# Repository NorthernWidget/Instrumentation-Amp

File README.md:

# Instrumentation-Amp

Breakout board for the AD623 instrumentation amplifier.

It is set up to work in either single-supply or dual-supply mode

## Single-supply mode

* Connect VC- (negative supply voltage) to GND using JP_VC- or the screw terminals

For sensors that require a simple common ground (including the reference), you will close the circuit across all of the solder jumpers:
* Connect VS- (negative voltage from device with signal to be amplified) to GND using JP_VS- or the screw terminals
* Connect Vref (reference voltage for the input signal) to GND using JP_VREF or the screw terminals

We use connect all of the jumpers to use a pyranometer.

### Dual-supply mode

We haven't had to use the board this way, but set it up to work!

* Disconnect VC- (negative supply voltage) from GND: check JP_VC- and the screw terminals
* Disconnect VS- (negative voltage from device with signal to be amplified) from GND: check JP_VS- and the screw terminals

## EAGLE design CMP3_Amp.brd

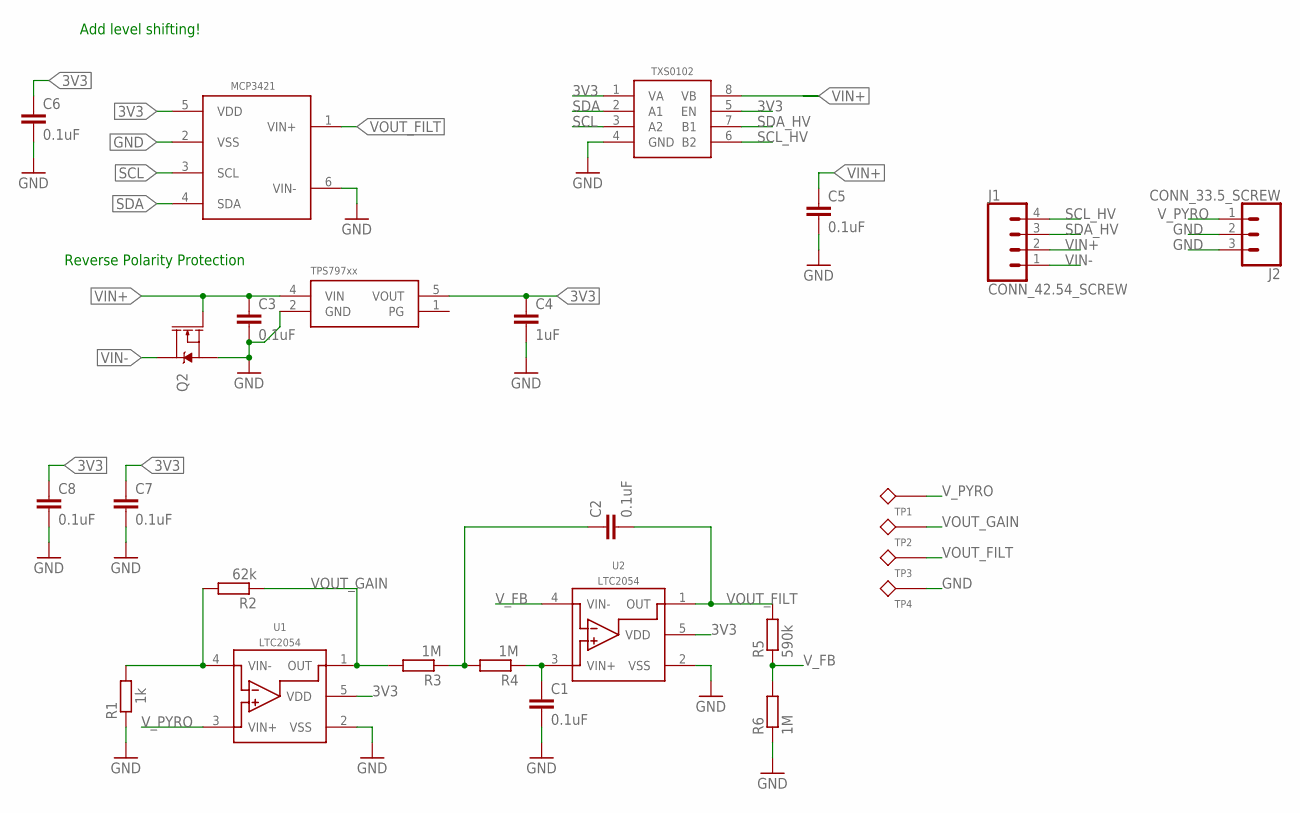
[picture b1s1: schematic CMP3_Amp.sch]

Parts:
C1, C2, C3: 0.1uF; C0603
C4: 1uF; C0603
C5, C6, C7, C8: 0.1uF; C0402
J1: CONN_42.54_SCREW; 1X04_SCREW
J2: CONN_33.5_SCREW; 1X03_3.5MM_SCREW
Q2: DMG3404; SOT23-3
R1: 1k; R0603
R2: 62k; R0603
R3, R4, R6: 1M; R0603
R5: 590k; R0603
TP1, TP2, TP3, TP4: TESTPOINTRCU; TESTPOINT_0603
U1, U2: LTC2054; SOT23-5
U3: MCP3421A1; SOT23-6L
U4: TXS0102DQM; DQM_R-PX2SON-N8
U5: TPS79733; DCK_R-PDSO-G5

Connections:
3V3: C4.1, C6.1, C7.1, C8.1, U1.5 (VDD), U2.5 (VDD), U3.5 (VDD), U4.1 (VA), U4.5 (EN), U5.5 (VOUT)
GND: C1.2, C3.2, C4.2, C5.2, C6.2, C7.2, C8.2, J2.2, J2.3, Q2.2 (S), R1.1, R6.1, TP4.1, U1.2 (VSS), U2.2 (VSS), U3.2 (VSS), U3.6 (VIN-), U4.4 (GND), U5.2 (GND)
unnamed: R1.2, R2.2, U1.4 (VIN-)
unnamed: C2.1, R3.1, R4.2
unnamed: C1.1, R4.1, U2.3 (VIN+)
SCL: U3.3 (SCL), U4.3 (A2)
SCL_HV: J1.4, U4.6 (B2)
SDA: U3.4 (SDA), U4.2 (A1)
SDA_HV: J1.3, U4.7 (B1)
VIN+: C3.1, C5.1, J1.2, Q2.1 (G), U4.8 (VB), U5.4 (VIN)
VIN-: J1.1, Q2.3 (D)
VOUT_FILT: C2.2, R5.2, TP3.1, U2.1 (OUT), U3.1 (VIN+)
VOUT_GAIN: R2.1, R3.2, TP2.1, U1.1 (OUT)
V_FB: R5.1, R6.2, U2.4 (VIN-)
V_PYRO: J2.1, TP1.1, U1.3 (VIN+)

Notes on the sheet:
Reverse Polarity Protection
Add level shifting!

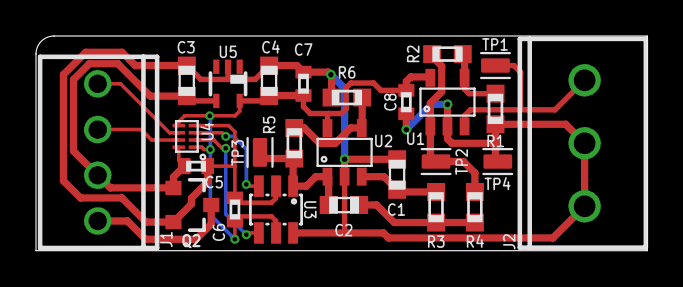
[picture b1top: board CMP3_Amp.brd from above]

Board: 2 copper layers, 34.0 x 11.9 mm, 26 parts (0 on the bottom side), 15 nets.

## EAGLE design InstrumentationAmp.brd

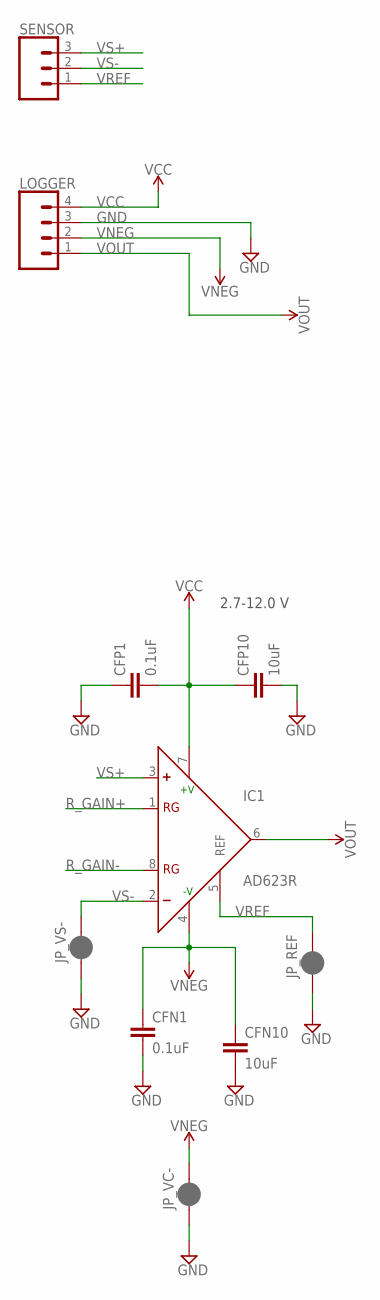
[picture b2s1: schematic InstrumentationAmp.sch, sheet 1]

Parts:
CFN1: 0.1uF; 0603
CFN10: 10uF; C0805
CFP1: 0.1uF; 0603
CFP10: 10uF; C0805
IC1: AD623R; SO8
JP_REF: JUMPER-SMT_2_NC_PASTE_SILK; SMT-JUMPER_2_NC_PASTE_SILK
JP_VC-: JUMPER-SMT_2_NC_PASTE_SILK; SMT-JUMPER_2_NC_PASTE_SILK
JP_VS-: JUMPER-SMT_2_NC_PASTE_SILK; SMT-JUMPER_2_NC_PASTE_SILK
LOGGER: CONN_04; 1X04
SENSOR: CONN_03; 1X03

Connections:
GND: CFN1.2, CFN10.2, CFP1.1, CFP10.2, JP_REF.1, JP_VC-.1, JP_VS-.1, LOGGER.3; also elsewhere on the board
R_GAIN+: IC1.1 (RG); also elsewhere on the board
R_GAIN-: IC1.8 (RG); also elsewhere on the board
VCC: CFP1.2, CFP10.1, IC1.7 (+V), LOGGER.4; also elsewhere on the board
VNEG: CFN1.1, CFN10.1, IC1.4 (-V), JP_VC-.2, LOGGER.2
VOUT: IC1.6 (OUT), LOGGER.1
VREF: IC1.5 (REF), JP_REF.2, SENSOR.1
VS+: IC1.3 (+), SENSOR.3
VS-: IC1.2 (-), JP_VS-.2, SENSOR.2

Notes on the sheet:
2.7-12.0 V

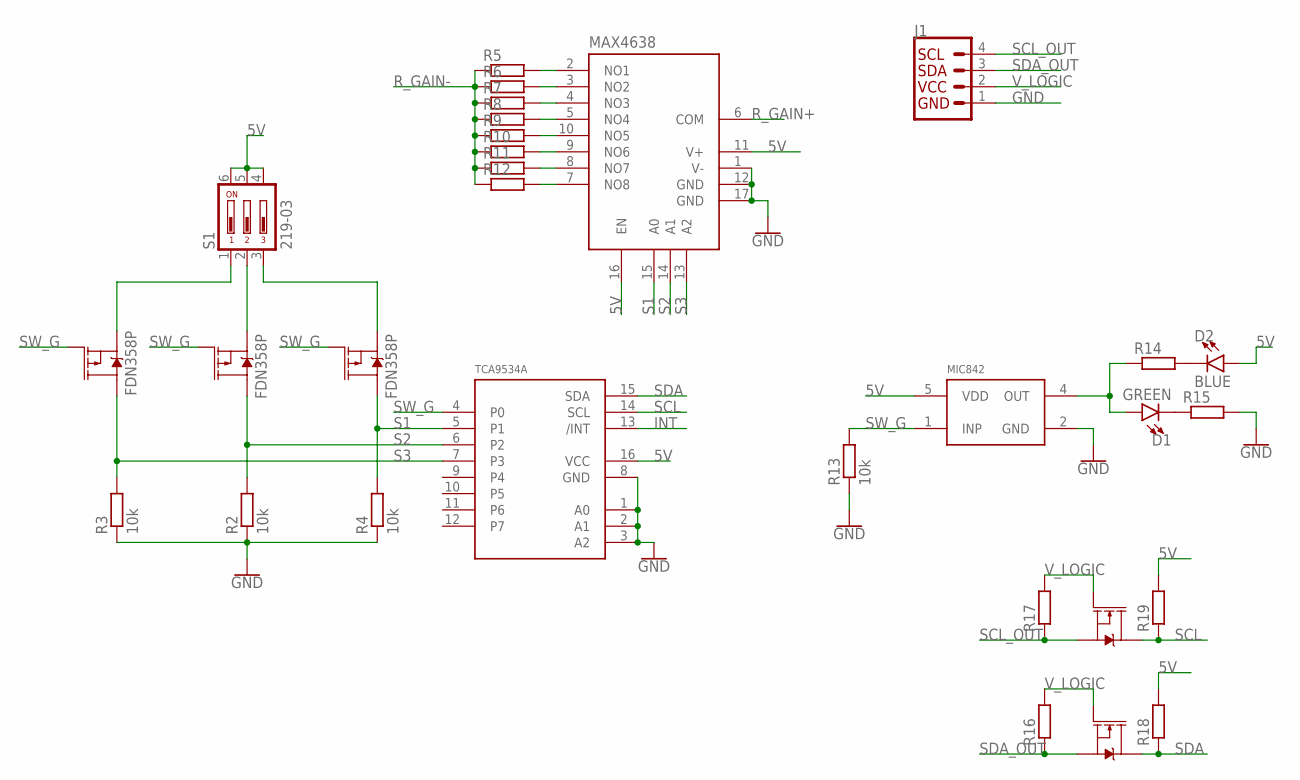
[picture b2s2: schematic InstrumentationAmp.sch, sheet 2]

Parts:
D1: GREEN; LED-0603
D2: BLUE; LED-0603
J1: I2C_STANDARD; 1X04
Q1, Q2: 310mA/60V/1.6Ω; SOT323
R2, R3, R4, R13: 10k; R0603
R5, R6, R7, R8, R9, R10, R11, R12, R14, R15, R16, R17, R18, R19: R-EU_R0603; R0603
S1: 219-03; CTS-219-03
U$1: MAX4638; TQFN16
U$2: TCA9534A; TSSOP16
U$3, U$4, U$5: FDN358P; SSOT-3
U$6: MIC842; DCK_R-PDSO-G5

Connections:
5V: D2.A, R18.2, R19.2, S1.4, S1.5, S1.6, U$1.11 (V+), U$1.16 (EN), U$2.16 (VCC), U$6.5 (VDD); also elsewhere on the board
GND: J1.1, R2.1, R3.1, R4.1, R13.1, R15.2, U$1.1 (V-), U$1.12 (GND), U$1.17 (GND), U$2.1 (A0), U$2.2 (A1), U$2.3 (A2), U$2.8 (GND), U$6.2 (GND); also elsewhere on the board
INT: U$2.13 (/INT)
unnamed: S1.2, U$4.2 (S)
unnamed: D2.C, R14.2
unnamed: S1.3, U$5.2 (S)
unnamed: S1.1, U$3.2 (S)
unnamed: R5.2, U$1.2 (NO1)
unnamed: R6.2, U$1.3 (NO2)
unnamed: R7.2, U$1.4 (NO3)
unnamed: R8.2, U$1.5 (NO4)
unnamed: R9.2, U$1.10 (NO5)
unnamed: R10.2, U$1.9 (NO6)
unnamed: R11.2, U$1.8 (NO7)
unnamed: R12.2, U$1.7 (NO8)
unnamed: D1.C, R15.1
unnamed: D1.A, R14.1, U$6.4 (OUT)
R_GAIN+: U$1.6 (COM); also elsewhere on the board
R_GAIN-: R5.1, R6.1, R7.1, R8.1, R9.1, R10.1, R11.1, R12.1; also elsewhere on the board
S1: R4.2, U$1.15 (A0), U$2.5 (P1), U$5.3 (D)
S2: R2.2, U$1.14 (A1), U$2.6 (P2), U$4.3 (D)
S3: R3.2, U$1.13 (A2), U$2.7 (P3), U$3.3 (D)
SCL: Q2.3 (D), R19.1, U$2.14 (SCL)
SCL_OUT: J1.4, Q2.2 (S), R17.1
SDA: Q1.3 (D), R18.1, U$2.15 (SDA)
SDA_OUT: J1.3, Q1.2 (S), R16.1
SW_G: R13.2, U$2.4 (P0), U$3.1 (G), U$4.1 (G), U$5.1 (G), U$6.1 (INP)
V_LOGIC: J1.2, Q1.1 (G), Q2.1 (G), R16.2, R17.2

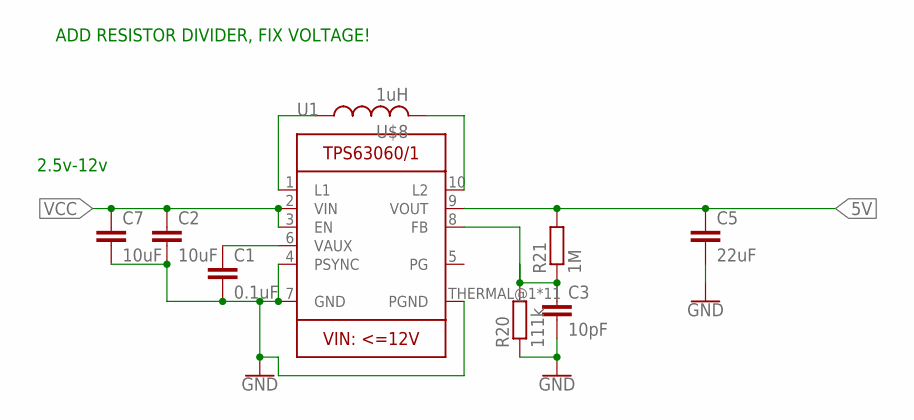
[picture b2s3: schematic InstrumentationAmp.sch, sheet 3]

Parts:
C1: 0.1uF; C0603
C2, C7: 10uF; C0805
C3: 10pF; C0603
C5: 22uF; C0805
R20: 111k; R0603
R21: 1M; R0603
U1: TPS63061; PWSON-N10
U$8: 1uH; WE-MAIA(4.1X4.1)

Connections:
5V: C5.1, R21.2, U1.9 (VOUT); also elsewhere on the board
GND: C1.2, C2.2, C3.2, C5.2, C7.2, R20.1, U1.4 (PSYNC), U1.7 (GND), U1.THERMAL@1 (PGND), U1.THERMAL@5 (PGND), U1.THERMAL@6 (PGND), U1.THERMAL@7 (PGND), U1.THERMAL@8 (PGND), U1.THERMAL@9 (PGND), U1.THERMAL@10 (PGND), U1.THERMAL@11 (PGND), U1.THERMAL@12 (PGND), U1.THERMAL@13 (PGND), U1.THERMAL@14 (PGND); also elsewhere on the board
unnamed: U1.1 (L1), U$8.P$1 (1)
unnamed: C3.1, R20.2, R21.1, U1.8 (FB)
unnamed: U1.10 (L2), U$8.P$2 (2)
unnamed: C1.1, U1.6 (VAUX)
VCC: C2.1, C7.1, U1.2 (VIN), U1.3 (EN); also elsewhere on the board

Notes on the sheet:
2.5v-12v
ADD RESISTOR DIVIDER, FIX VOLTAGE!

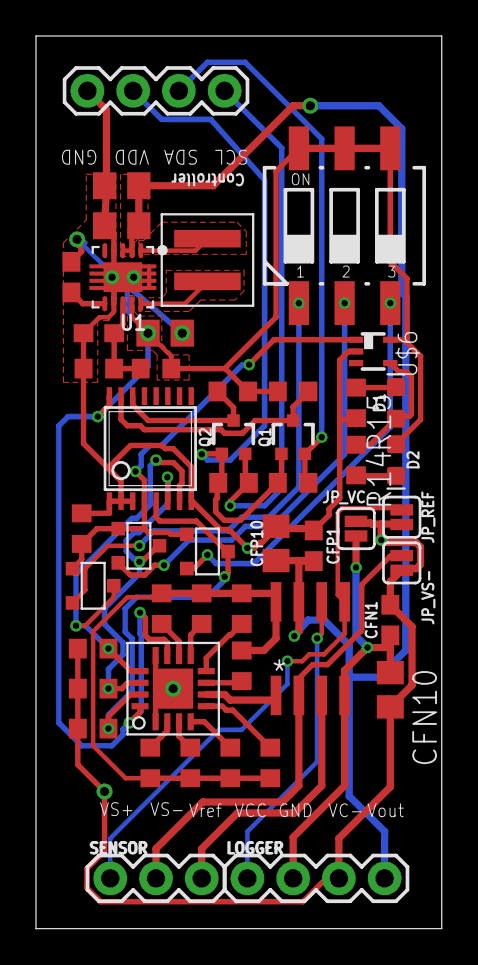
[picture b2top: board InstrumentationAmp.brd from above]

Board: 2 copper layers, 22.5 x 49.6 mm, 49 parts (0 on the bottom side), 37 nets.

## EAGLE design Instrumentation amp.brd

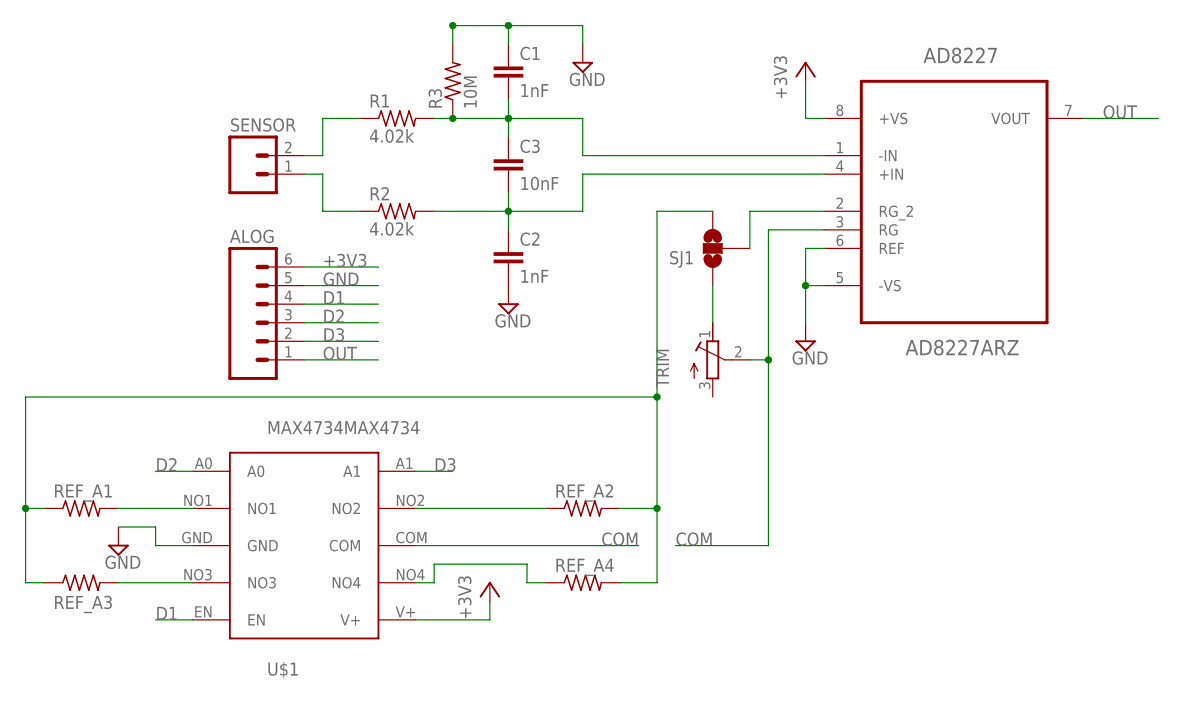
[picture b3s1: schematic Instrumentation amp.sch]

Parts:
AD8227: AD8227ARZ; SOIC127P600X175-8N
ALOG: M063.5MM-6; SCREWTERMINAL-3.5MM-6
C1, C2: 1nF; C0805
C3: 10nF; C0805
R1, R2: 4.02k; M0805
R3: 10M; M0805
REF_A1, REF_A2, REF_A3, REF_A4: R-US_0207/10; 0207/10
SENSOR: M023.5MM; SCREWTERMINAL-3.5MM-2
SJ1: SOLDERJUMPER_2WAYS; SJ_3
TRIM: R-TRIMM3006P; RTRIM3006P
U$1: MAX4734MAX4734; UMAX-10

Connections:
+3V3: AD8227.8 (+VS), ALOG.6, U$1.V+
COM: AD8227.3 (RG), TRIM.2 (S), U$1.COM
D1: ALOG.4, U$1.EN
D2: ALOG.3, U$1.A0
D3: ALOG.2, U$1.A1
GND: AD8227.5 (-VS), AD8227.6 (REF), ALOG.5, C1.1, C2.2, R3.2, U$1.GND
unnamed: AD8227.1 (-IN), C1.2, C3.1, R1.2, R3.1
unnamed: AD8227.4 (+IN), C2.1, C3.2, R2.2
unnamed: REF_A1.2, U$1.NO1
unnamed: REF_A3.2, U$1.NO3
unnamed: REF_A2.1, U$1.NO2
unnamed: R1.1, SENSOR.2
unnamed: REF_A4.1, U$1.NO4
unnamed: R2.1, SENSOR.1
unnamed: REF_A1.1, REF_A2.2, REF_A3.1, REF_A4.2, SJ1.3
unnamed: SJ1.1, TRIM.1 (A)
unnamed: AD8227.2 (RG_2), SJ1.2
OUT: AD8227.7 (VOUT), ALOG.1

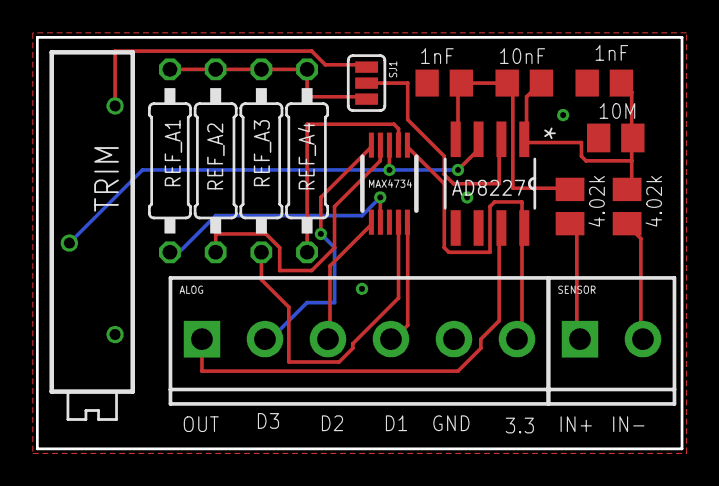
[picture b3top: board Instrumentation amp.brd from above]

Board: 2 copper layers, 35.8 x 22.9 mm, 16 parts (0 on the bottom side), 18 nets.

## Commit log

2016-07-19 Version one of instrumentation amplifier
2016-07-20 Improved tracing and changes for OSH Park compliance
2016-08-11 Changed ground, added ground fill to top layer
2017-06-27 AD623R Redesign
2017-06-27 Datasheet
2017-06-27 Deprecated
2017-06-27 Rough BoM
2017-06-27 Names match README; connect Vref
2017-06-27 ERC, DRC
2017-06-27 Pin 1 marker
2017-07-18 Initial layout of Amp 2.0
    Changed schematic to add on board buck-boost converter, mux to control gain, and I2C IO expander to allow gain to be controlled via I2C. Preliminary layout complete, ready for verification
2017-07-19 Fixed spacing for screw terminals, ready for final check
    Moved the screw terminals and silk screen to support screw terminal sizes, fixed one air wire on board layout, ready for final check before ordering
2017-09-05 upload gerbers
2017-09-26 Added layer 112 tsilk
2017-10-26 Made Edits from 1st round of board testing
    Flipped direciton of PFETs, fixed switch mode regulator package, changed capacitor sizes, chained set resistor values, etc. Verification still required that all changes are made
2017-11-06 Fixed some DRC errors, added to ground plane
    Made additions to power ground plane, fixed releveant DRC errors, ready for checking
2017-11-06 Added Silkscreen model ID
2017-11-07 added gerber files
2017-11-07 changes to header and silkscreen labels
2017-11-07 move brd file out of gerber folder
2018-06-17 CC-BY-SA
2018-11-20 Board assembly photos for inst amp
2018-11-20 Added dedicated CMP3
    Added an updated digital interface amplifier specifically designed for the Kipp and Zonen CMP3
2018-11-20 Initial layout of CMP3 Amp
    Layout of CMP3 amp complete, requires review and gerber generation before being sent to fab
2018-11-20 Updated silk screen
2018-11-20 Added Gerbers
2018-11-26 Generated Gerbers, Minor Updates
2018-11-27 Added simulations for CMP3 Amp
    Also added LTSpice files to gitignore
2018-11-30 Updated part numbers for CMP3 Amp
    Updated part numbers for CMP3 amp and made changes to the CMP3 amp simulation

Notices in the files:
parts and their libraries:
SparkFun-Connectors: Licensing: Creative Commons ShareAlike 4.0 International - https://creativecommons.org/licenses/by-sa/4.0
